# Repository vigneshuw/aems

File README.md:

# AEMS — Autonomous Energy Monitoring System

An open-source, low-cost, modular platform for high-resolution energy monitoring of manufacturing equipment. AEMS acquires three-phase voltage and current through a front end and a 24-bit, simultaneously sampling ADC, managed by a dual-core architecture that separates deterministic acquisition and on-board logging from host communication and control. A host, edge-gateway, and optional cloud software stack enable autonomous, long-duration acquisition independent of a continuously connected host, combining research-grade fidelity with industrial deployability for Industry 4.0 environments.

This repository accompanies the paper (preprint):

> **An Open-Source, Autonomous Platform for High-Resolution Energy Monitoring in Manufacturing**
> Vignesh Selvaraj, Aditya Nagaraj, Shengyuan Zhang, Sina Sadeghian, Sangkee Min

If you use this hardware, firmware, or software in your work, please see
[Citation](#citation) and [`CITATION.cff`](CITATION.cff).

---

## Why AEMS

Long-term, robust monitoring of machine energy consumption is difficult: commercial power
meters capable of capturing transient events are expensive, closed, and impractical to deploy
across an entire facility. AEMS was designed to make high-fidelity energy monitoring
**affordable, customizable, and reproducible**, so that small and medium-sized manufacturers
can instrument their equipment and improve data availability for Industry 4.0 analytics.

Design goals:

- **High-rate, simultaneous multi-channel acquisition** of voltage and current signals.
- **Autonomous operation** — capture and log on the board even when a host or network is unavailable, then stream or transfer data later.
- **Modular and open** — hardware, firmware, and host software are all open and independently reusable.
- **Deployable at scale** — many boards can share a network and be controlled from a single host or from an edge computer such as Raspberry Pi.

---

## System overview

AEMS is organized into three layers, each of which lives in this repository:

| Layer | Location | Role |
|---|---|---|
| **Hardware** | [`hardware/`](hardware/) | Custom AEMS v2 DAQ board — KiCad design, ADS131M08 analog front end, surge protection, impedance-controlled PCB. |
| **Firmware** | [`firmware/`](firmware/) | STM32H745 dual-core firmware. **CM4** owns deterministic acquisition + eMMC storage; **CM7** owns Ethernet/TCP + host command/control over OpenAMP. |
| **Host software** | [`firmware/BoardInterfaceLibrary/`](firmware/BoardInterfaceLibrary/) | Python `board_interface` library, examples, Raspberry Pi daemon (`aemsctl`), and an optional AWS IoT cloud agent. |

```
Machine mains ──▶ AEMS board (ADS131M08 front end)
                        │
                   STM32H745
              ┌─────────┴─────────┐
        CM4 (DAQ + eMMC)   CM7 (Ethernet/TCP)
                        │
                Host (PC / Raspberry Pi)
             board_interface  ·  aemsctl daemon
```

Data flows from the analog front end through the ADS131M08 acquisition path on CM4, is logged
to on-board eMMC and/or streamed over TCP to a host, and can optionally be forwarded to the
cloud for remote monitoring and transfer.

---

## Repository layout

```
aems/
├── hardware/                     KiCad project for the AEMS v2 board
│   ├── *.kicad_sch / *.kicad_pcb Schematics and PCB layout
│   ├── CustomLibs/               Project symbol/footprint libraries
│   ├── LTSpiceSimulation/        Analog front-end simulations (CT op-amp, etc.)
│   ├── DesignSummary/            Stackup, impedance control, interactive BOM (ibom.html)
│   ├── Manufacturing/            PCBWay fabrication outputs
│   └── FutureUpdates/            Planned revisions (e.g. front-end isolation)
│
└── firmware/                     STM32H745 dual-core firmware + host tooling
    ├── CM4/                      Cortex-M4: DAQ, ADS131M08, eMMC/FatFs, OpenAMP
    ├── CM7/                      Cortex-M7: Ethernet/TCP, FreeRTOS, OpenAMP master
    ├── Common/                   Shared cross-core headers/data structures
    ├── BoardInterfaceLibrary/    Python host library, CLI, Raspberry Pi daemon, cloud agent
    ├── docs/Software/            Firmware architecture documentation
    └── UnitTests/                Bench connectivity/test scripts
```

Detailed documentation already lives with each subtree:

- **Firmware architecture** — [`firmware/README.md`](firmware/README.md) and
  [`firmware/docs/Software/README.md`](firmware/docs/Software/README.md)
- **Host Python library** — [`firmware/BoardInterfaceLibrary/README.md`](firmware/BoardInterfaceLibrary/README.md)
- **Raspberry Pi server & cloud** —
  [`firmware/BoardInterfaceLibrary/docs/raspberry_pi_server.md`](firmware/BoardInterfaceLibrary/docs/raspberry_pi_server.md),
  [`firmware/BoardInterfaceLibrary/docs/cloud_autonomy.md`](firmware/BoardInterfaceLibrary/docs/cloud_autonomy.md)
- **Hardware** — [`hardware/README.md`](hardware/README.md)

---

## Hardware at a glance

The AEMS v2 board is built around:

- **ADS131M08** 8-channel, 24-bit simultaneous-sampling delta-sigma ADC as the analog front end.
- **STM32H745** dual-core (Cortex-M7 + Cortex-M4) microcontroller.
- **Isolated power rails** and impedance-controlled routing for Ethernet and USB.
- **MOV-based surge protection** on the measurement inputs.
- **On-board eMMC** storage for logging, plus Ethernet connectivity.

The current firmware and host workflows target a **6-channel acquisition mask (`0x3F`)** — three voltage and three current channels. See [`hardware/README.md`](hardware/README.md) for the board description, bill of materials, and manufacturing notes.

> **Note on voltage range:** the present hardware is validated for direct measurement at the
> board's rated input topology. Higher line-to-line service voltages (e.g. 480 V L-L) require updating the MOV-based surge protector or an external potential transformer, consistent with the modular design; see
> [`hardware/FutureUpdates/`](hardware/FutureUpdates/).

---

## Getting started

The fastest path depends on what you want to do.

**Bring up a board and capture data**

1. Read the system split in [`firmware/docs/Software/README.md`](firmware/docs/Software/README.md).
2. Build and flash the CM4/CM7 firmware from STM32CubeIDE ([`firmware/`](firmware/)).
3. Confirm connectivity with `firmware/UnitTests/tcptest.py` or the Python examples.
4. Use the [`board_interface`](firmware/BoardInterfaceLibrary/) library for repeatable host-side
   control, logging, and streaming.

**Reproduce or modify the hardware**

1. Open the KiCad project in [`hardware/`](hardware/).
2. Review the interactive BOM at `hardware/DesignSummary/ibom.html` and the stackup/impedance
   summaries.
3. Use the [`hardware/Manufacturing/`](hardware/Manufacturing/) outputs for fabrication.

**Deploy a permanent Raspberry Pi server**

See [`firmware/BoardInterfaceLibrary/docs/raspberry_pi_server.md`](firmware/BoardInterfaceLibrary/docs/raspberry_pi_server.md)
for the `aems-boardd` systemd daemon and `aemsctl` control command, and
[`cloud_autonomy.md`](firmware/BoardInterfaceLibrary/docs/cloud_autonomy.md) for optional AWS
IoT integration.

---

## Repository provenance

`hardware/` and `firmware/` are maintained as independent projects and integrated here via
`git subtree`. Each retains its own commit history and can be developed in isolation.

---

## Citation

If you use AEMS in academic work, please cite the paper and (optionally) the archived software
release. Machine-readable metadata is in [`CITATION.cff`](CITATION.cff).

```bibtex
@misc{selvaraj_aems_2026,
  title   = {An Open-Source, Autonomous Platform for High-Resolution Energy
             Monitoring in Manufacturing},
  author  = {Selvaraj, Vignesh and Nagaraj, Aditya and Zhang, Shengyuan and
             Sadeghian, Sina and Min, Sangkee},
  year    = {2026},
  note    = {Preprint. Department of Mechanical Engineering,
             University of Wisconsin-Madison}
  % arXiv id / journal / doi to be added
}
```

The software itself is archived on Zenodo. Please cite the concept DOI (resolves to the
latest release):

**DOI: [10.5281/zenodo.21383443](https://doi.org/10.5281/zenodo.21383443)**

```bibtex
@software{selvaraj_aems_software,
  author    = {Selvaraj, Vignesh and Nagaraj, Aditya and Zhang, Shengyuan and
               Sadeghian, Sina and Min, Sangkee},
  title     = {AEMS: Autonomous Energy Monitoring System},
  year      = {2026},
  publisher = {Zenodo},
  doi       = {10.5281/zenodo.21383443},
  url       = {https://github.com/vigneshuw/aems}
}
```

The version validated in the paper is v1.0.2 (DOI: [10.5281/zenodo.21383444](https://doi.org/10.5281/zenodo.21383444)).

---

## License

AEMS is released as open hardware and open-source software under a per-material split (full
texts in [`LICENSES/`](LICENSES/), following the [REUSE](https://reuse.software) convention):

| Material | License | Applies to |
|---|---|---|
| Hardware design files | [`CERN-OHL-P-2.0`](LICENSES/CERN-OHL-P-2.0.txt) | [`hardware/`](hardware/) — schematics, PCB, libraries, BOM, fabrication outputs |
| Firmware & host software | [`MIT`](LICENSES/MIT.txt) | original code in [`firmware/`](firmware/) and the Python `BoardInterfaceLibrary` |
| Documentation & figures | [`CC-BY-4.0`](LICENSES/CC-BY-4.0.txt) | READMEs, `docs/`, design summaries |

SPDX expression for the repository: `CERN-OHL-P-2.0 AND MIT AND CC-BY-4.0`. Vendor and
third-party components (ST HAL/CMSIS, FreeRTOS, OpenAMP, FatFs, BlueNRG-2, downloaded KiCad
libraries) retain their own licenses. See [`LICENSE`](LICENSE) for the full overview.

---

## Contact

**Vignesh Selvaraj** — `vselvaraj@wisc.edu`, `vignesh-selvaraj@outlook.com`

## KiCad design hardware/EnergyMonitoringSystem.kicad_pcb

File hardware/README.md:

# AEMS Hardware — Energy Monitoring System Board

KiCad design for the AEMS v2 data-acquisition board: a custom, multi-channel energy-monitoring
front end built around the **ADS131M08** ADC and the **STM32H745** dual-core MCU. This is the
hardware layer of the [Autonomous Energy Monitoring System](../README.md) and is designed to be
reproduced, modified, and manufactured by others.

The KiCad project root is `EnergyMonitoringSystem.kicad_pro`.

---

## Board overview

The board acquires multi-channel voltage and current signals at a high, simultaneous sampling
rate, digitizes them through the ADS131M08 analog front end, and hands the data to the STM32H745
for on-board logging and network streaming.

Key design features:

- **ADS131M08** — 8-channel, 24-bit, simultaneous-sampling delta-sigma ADC front end.
- **STM32H745** dual-core (Cortex-M7 + Cortex-M4) host MCU with eMMC and Ethernet.
- **Isolated power rails** feeding the analog front end and digital domains.
- **Impedance-controlled, multilayer PCB** (100 Ω differential / 50 Ω single-ended Ethernet,
  90 Ω USB) — see the impedance and stackup exports in [`DesignSummary/`](DesignSummary/).
- **MOV-based surge protection** on the measurement inputs.
- **Ethernet** and **on-board eMMC** for autonomous, network-independent logging.

The current firmware/host workflows use a **6-channel acquisition mask (`0x3F`)** — three voltage and three current channels.

> **Input voltage topology:** the present design is validated for its rated direct-measurement
> input topology. Measuring higher line-to-line service voltages (e.g. 480 V L-L) exceeds the
> on-board MOV continuous ratings and requires an updated **MOV surge protector (upto a certain voltage level)** or **external potential transformer**. This is
> consistent with the modular design intent and is tracked under
> [`FutureUpdates/`](FutureUpdates/).

---

## Board Power-Up

Temporarily, due to a design issue, the board needs to be powered on as shown in the figure below. This design issue will be fixed in the next hardware version. 

---

## Project structure

```
hardware/
├── EnergyMonitoringSystem.kicad_pro   KiCad project
├── EnergyMonitoringSystem.kicad_sch   Root schematic
├── EnergyMonitoringSystem.kicad_pcb   PCB layout
├── *.kicad_sch                        Hierarchical sheets (see below)
├── CustomLibs/                        Project symbol/footprint libraries
│   ├── EMS.kicad_sym                  Custom symbols
│   ├── EMS.pretty/                    Custom footprints
│   └── Downloaded/                    Third-party part libs (ADS131M08, MOV, op-amps, …)
├── LTSpiceSimulation/                 Analog front-end simulations (CT op-amp, rough studies)
├── Datasheets/                        Component reference material
├── ApplicationNotes/                  ST H7 hardware development notes
├── DesignSummary/                     Stackup, impedance control, interactive BOM
├── Manufacturing/PCBWay/              Fabrication + assembly outputs (Gerbers, drill, BOM, CPL)
└── FutureUpdates/Planned/             Planned revisions (front-end isolation, etc.)
```

### Schematic sheets

The design is hierarchical. The main functional sheets are:

| Sheet | Function |
|---|---|
| `adc` | ADS131M08 analog front end and signal conditioning |
| `uC` / `uCMain` | STM32H745 microcontroller and support |
| `ethernet` | Ethernet PHY (LAN8742) and magnetics |
| `poe` | Ethernet input (No PoE setup currently) |
| `vr` | Voltage regulation / power rails |
| `emmc` | eMMC storage |
| `sd_card` | SD card interface |
| `usb` | USB interface |
| `bm` | Bluetooth (BlueNRG) module |

---

## Bill of materials

- **Interactive BOM:** open [`DesignSummary/ibom.html`](DesignSummary/ibom.html) in a browser
  for a searchable, click-to-highlight BOM with board placement.
- **Fabrication BOM / placement:**
  [`Manufacturing/PCBWay/EnergyMonitoringSystem.kicad_pcb/PCBWay_bom.csv`](Manufacturing/PCBWay/EnergyMonitoringSystem.kicad_pcb/PCBWay_bom.csv)
  and `PCBWay_positions.csv` (component placement / CPL).

---

## Manufacturing

Ready-to-fabricate outputs (generated for PCBWay) are in
[`Manufacturing/PCBWay/`](Manufacturing/PCBWay/) or you generated your own from the KiCAD project:

- Gerbers (`F_Cu`, `B_Cu`, `In1..In6_Cu`, mask, paste, silkscreen, edge cuts)
- Drill files (`PTH`, `NPTH`)
- `PCBWay_bom.csv` (BOM) and `PCBWay_positions.csv` (pick-and-place)
- `PCBWay_netlist.ipc` (IPC-356 netlist)
- `DesignRequirements.pdf` and `Jump-SolderBridges.png` (assembly notes)

Stackup and impedance targets are documented in [`DesignSummary/`](DesignSummary/)
(`CurrentStackup.png`, `PCBWay Stackup.png`, and the `ImpedanceControl *.png` exports).

To regenerate outputs, open `EnergyMonitoringSystem.kicad_pcb` in KiCad and re-plot Gerbers/drill
and re-export the BOM/placement.

---

## Requirements

- **KiCad 7** or newer to open the project.
- Custom and downloaded libraries under [`CustomLibs/`](CustomLibs/) are referenced via the
  project-local `sym-lib-table` / `fp-lib-table`, so the project should open self-contained.

---

## Future updates

Planned hardware revisions are tracked in [`FutureUpdates/Planned/`](FutureUpdates/Planned/),
including improved analog front-end **isolation** and higher line-to-line voltages.

---

## License

Hardware licensing is being finalized as part of the open-hardware release; see the
[top-level LICENSE](../LICENSE). Please contact the authors before redistributing the design
files until the final license is committed.

For system context, firmware, and host software, see the [top-level README](../README.md).

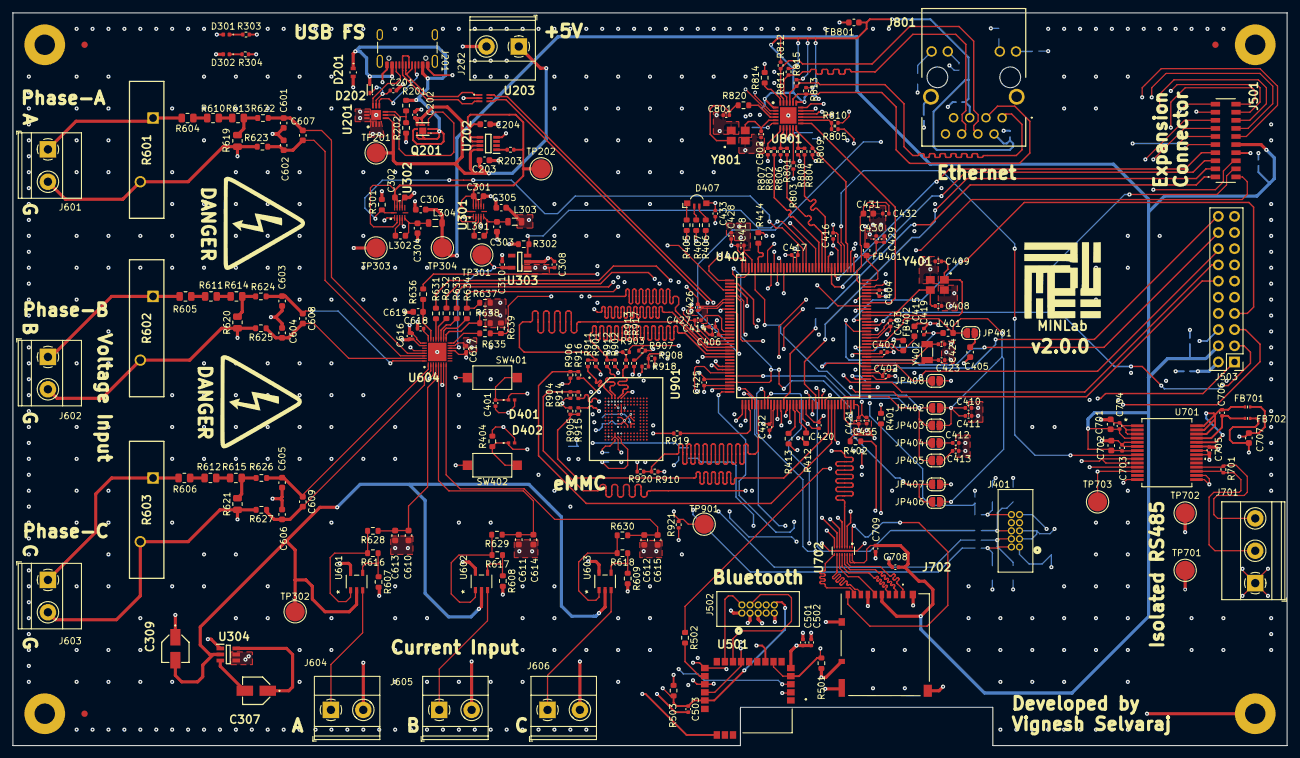
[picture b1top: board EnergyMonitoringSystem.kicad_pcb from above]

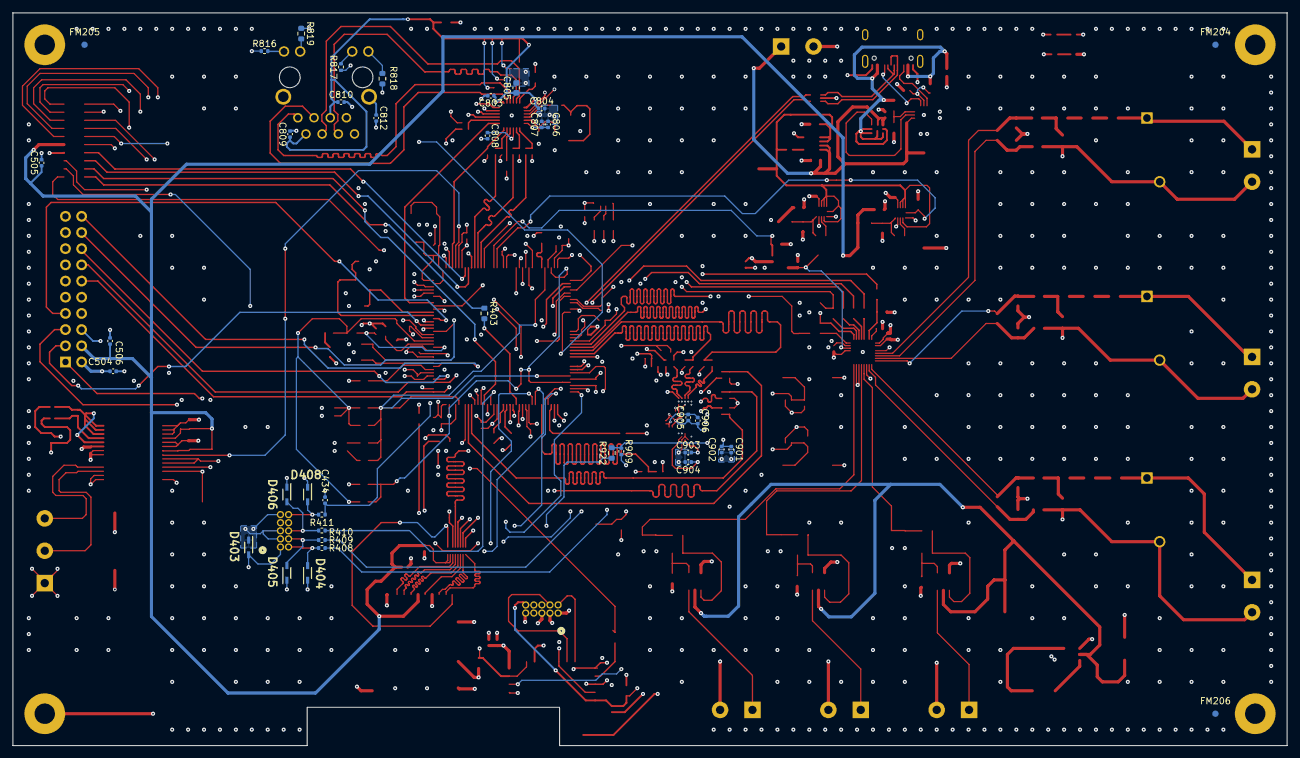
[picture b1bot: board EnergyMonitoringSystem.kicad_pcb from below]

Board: 8 copper layers, 200.0 x 115.0 mm, 294 parts (38 on the bottom side), 213 nets.

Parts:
C201, C202, C401, C402, C403, C404, C407, C414, C416, C417, C418, C420, C421, C422, C425, C426, C427, C430, C432, C433, C434, C502, C503, C504, C505, C506, C708, C709, C803, C804, C808, C809, C810, C901, C903, C905: 100n; C_0402_1005Metric
C203, C204, C301, C302, C405, C415, C431, C701, C702, C707, C805: 10u; C_0603_1608Metric
C303, C304, C305, C306: 47u; C_0603_1608Metric
C307, C309: 10u; 10SVPS10M
C308, C310, C406, C429, C616, C617, C807: 1u; C_0402_1005Metric
C408, C409, C423, C424, C801, C802: 5p6; C_0402_1005Metric
C410, C411: 4u7; C_0402_1005Metric
C412, C413, C428, C435, C501, C902, C904, C906: 2u2; C_0402_1005Metric
C419: 220p; C_0402_1005Metric
C601, C602, C603, C604, C605, C606, C610, C611, C612, C619: 10p; C_0603_1608Metric
C607, C608, C609, C613, C614, C615: 6800p; C_0603_1608Metric
C618: 220n; C_0402_1005Metric
C703, C704, C705, C706: 0u1; C_0402_1005Metric
C806: 470p; C_0402_1005Metric
C812: 1n; C_0402_1005Metric
D201: ESDA7P60-1U1M
D202: BAT30KFILM
D301, D302: LED; LED_0402_1005Metric
D401, D402: ESDALC6V1-1M2; ESDALC6V11M2
D403, D404, D405, D406, D408: PESD3V3L1BA,115; PESD3V3L1BA_115-SOD-323-2
D407: LED_RAGB; LED_Kingbright_APFA3010_3x1.5mm_Horizontal
FB401, FB402, FB801: FerriteBead; L_0603_1608Metric
FB701, FB702: FerriteBead; BLM15HD182SN1D
FM201, FM202, FM203, FM204, FM205, FM206: Fiducial; Fiducial_1mm_Mask2mm
H201, H202, H203, H204: MountingHole_Pad; MountingHole_3.2mm_M3_Pad
J201: USB_C_Receptacle_USB2.0_16P; USB_C_Receptacle_GCT_USB4105-xx-A_16P_TopMnt_Horizontal
J202, J601, J602, J603, J604, J605, J606: Screw_Terminal_01x02; TerminalBlock_Phoenix_MKDS-1,5-2-5.08_1x02_P5.08mm_Horizont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
J401, J502: Conn_02x05_Counter_Clockwise; 62701021621
J501: CLP-110-02-G-D; CLP-110-02-XXX-D
J503: Conn_02x08_Counter_Clockwise; PinHeader_2x10_P2.54mm_Vertical
J701: Screw_Terminal_01x03; TerminalBlock_Phoenix_MKDS-1,5-3-5.08_1x03_P5.08mm_Horizont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
J702: DM3AT-SF-PEJM5_40_; DM3ATSFPEJM540
J801: SI-60062-F; Connector-SI60062F
JP401, JP402, JP403, JP406, JP408: SolderJumper_2_Bridged; SolderJumper-2_P1.3mm_Open_RoundedPad1.0x1.5mm
JP404, JP405, JP407: SolderJumper_2_Open; SolderJumper-2_P1.3mm_Open_RoundedPad1.0x1.5mm
L301, L302, L401: 2u2; L_0603_1608Metric
L303, L304: 10u; L_0805_2012Metric
Q201: STL6N3LLH6
R201, R404, R607, R608, R609, R637: 10k; R_0603_1608Metric
R202: 2k7; R_0603_1608Metric
R203, R701: 120R; R_0402_1005Metric
R301, R302, R638, R639: 100k; R_0603_1608Metric
R303, R304: 220R; R_0402_1005Metric
R401, R402, R403, R502: 22R; R_0603_1608Metric
R405, R406, R407, R622, R623, R624, R625, R626, R627: 1k; R_0603_1608Metric
R408, R409, R410, R411, R811, R812, R813, R815: 49R9; R_0402_1005Metric
R412, R413, R414, R631, R632, R633, R634, R635, R636: 33R; R_0603_1608Metric
R501: 47k; R_0603_1608Metric
R503: 4k7; R_0603_1608Metric
R601, R602, R603: R_Variable; B72220S0271K101
R604, R605, R606, R610, R611, R612, R613, R614, R615: 330k; R_0805_2012Metric
R616, R617, R618: 15k; R_0603_1608Metric
R619, R620, R621: 750R; R_0805_2012Metric
R628, R629, R630: 2k; R_0603_1608Metric
R801, R802, R804, R805: 33R; R_0402_1005Metric
R803, R806, R807, R808, R810, R816, R817, R910: 10k; R_0402_1005Metric
R809: 1k5; R_0402_1005Metric
R814: 12k1; R_0603_1608Metric
R818, R819: 270R; R_0603_1608Metric
R820, R922: 0R; R_0603_1608Metric
R901, R902, R903, R904, R905, R906, R907, R908, R909, R921: 47k; R_0402_1005Metric
R911, R912, R913, R914, R915, R916, R917, R918, R919, R920: 22R; R_0402_1005Metric
SW401, SW402: SW_Push; SW_SPST_CK_RS282G05A3
TP201, TP202, TP301, TP302, TP303, TP304, TP701, TP702, TP703, TP901: TestPoint; TestPoint_Pad_D3.0mm
U201: TCPP01-M12; TCPP01-M12-QFN-12L
U202: STEF05SGR; STEF05SGR-TSOT23-8L
U203: USBLC6-2P6; USBLC62P6-SOT666-6
U301, U302: ST1PS02CQTR
U303: LDLN025M12R; LDLN025M12R-SOT-23-5
U304: LM2664M6_NOPB; LM2664M6_NOPB-SOT-23-6
U401: STM32H745ZGT6; STM32H745ZGT6_LQFP144
U501: BLUENRG-M2SA
U601, U602, U603: TSV911ILT; TSV911ILT_SOT23-5
U604: ADS131M08IRSNR; ADS131M08IRSNR-QFN40
U701: ADM2565EBRNZ; ADM2565EBRNZ-SOIC-28
U702: EMIF06-MSD02N16
U801: LAN8742A-CZ-TR; LAN8742A-CZ-TR_QFN50
U901: MX52LM04A11XSI; MX52LM04A11XSI_BGA153
Y401, Y801: Crystal_GND24; NX3225SA25000MSTDCSR6
Y402: 32.768KHz; Crystal_SMD_3215-2Pin_3.2x1.5mm

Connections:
+1V2: C310.1, TP301.1, U303.5 (OUT), U604.14 (REFIN)
+5V: C204.1, C301.1, C302.1, R203.1, TP202.1, U202.5 (SOURCE_1), U202.6 (SOURCE_2), U301.2 (VIN), U301.9 (D0), U301.10 (D1), U301.11 (D2), U301.12 (EN), U302.2 (VIN), U302.9 (D0), U302.10 (D1), U302.11 (D2)
+5V_EXT: C202.1, C203.1, J202.1, Q201.4 (S_1), Q201.8 (S_2), TP201.1, U201.4 (SOURCE), U202.7 (VCC_1), U202.8 (VCC_2)
+DCDC_1: C305.1, C308.1, C402.1, C403.1, C404.1, C406.1, C407.1, C414.1, C416.1, C417.1, C418.1, C420.1, C421.1, C422.1, C425.1, C426.1, C427.1, C428.2, C433.1, C435.2, C501.1, C502.1, C504.1, C616.2, C617.2, C808.1, C903.1, C904.1, C905.1, C906.1, D301.2 (A), D403.2 (K2), D407.2 (A), FB401.1, FB402.1, FB801.1, J401.1, J502.1, J503.2, JP407.1 (A), JP408.1 (A), L303.2, R503.2, R637.2, R638.2, R639.2, R806.2, R807.2, R808.2, R809.2, R810.2, R901.2, R902.2, R903.2, R904.2, R905.2, R906.2, R907.2, R908.2, R909.2, R910.2, SW402.2, TP303.1, U303.1 (IN), U304.4 (SD), U304.5 (V+), U401.7 (VDD_1), U401.13 (VDD_2), U401.19 (VDD_3), U401.32 (VDD_4), U401.42 (VDD_5), U401.56 (VDD_6), U401.71 (VDD_7), U401.79 (VDD_8), U401.90 (VDD50USB), U401.91 (VDD33USB), U401.92 (VDD_9), U401.106 (VDD_10), U401.119 (VDD_11), U401.129 (VDD_12), U401.144 (VDD_13), U501.5 (VIN), U601.5 (VCC+), U602.5 (VCC+), U603.5 (VCC+), U604.15 (AVDD), U604.26 (DVDD), U801.9 (VDDIO), U901.C6 (VCCQ_1), U901.E6 (VCC_1), U901.F5 (VCC_2), U901.J10 (VCC_3), U901.K9 (VCC_4), U901.M4 (VCCQ_2), U901.N4 (VCCQ_3), U901.P3 (VCCQ_4), U901.P5 (VCCQ_5)
+DCDC_2: C306.1, C505.1, C506.1, C701.1, C702.2, C703.1, C704.2, C708.1, C709.1, D302.2 (A), J501.10, J503.4, J702.4 (VDD), L304.2, TP304.1, U701.4 (VCC), U701.7 (VIO), U702.15 (VCC), U702.16 (RDATA_VCC)
+VBUSc: D201.1 (K), D202.2 (A), J201.A4 (VBUS), J201.A9 (VBUS), J201.B4 (VBUS), J201.B9 (VBUS), Q201.1 (D_1), Q201.2 (D_2), Q201.5 (D_3), Q201.6 (D_4), Q201.7 (D_5), R201.1
+VDD_SDC: C410.2, C411.2, JP401.2 (B), JP402.1 (A), JP403.1 (A), JP406.1 (A), L401.1, U401.17 (VFBSMPS)
+VREF: C429.1, C430.1, C431.1, C432.1, FB401.2, U401.35 (VREF+), U401.36 (VDDA)
+V_ISO: C705.1, C707.2, FB702.2, TP701.1, U701.23 (VISOIN)
-DCDC_1: C309.2, TP302.1, U304.2 (OUT), U601.2 (VCC-), U602.2 (VCC-), U603.2 (VCC-)
/ADC/CLKIN_ADS_T: C619.1, R636.2, U604.23 (XTAL1_CLKIN)
/ADC/CT_PhaseA_Amp_OUT: R616.2, R628.2, U601.1 (OUT)
/ADC/CT_PhaseA_IN: J604.1, U601.3 (IN+)
/ADC/CT_PhaseB_Amp_OUT: R617.2, R629.2, U602.1 (OUT)
/ADC/CT_PhaseB_IN: J605.1, U602.3 (IN+)
/ADC/CT_PhaseC_Amp_OUT: R618.2, R630.2, U603.1 (OUT)
/ADC/CT_PhaseC_IN: J606.1, U603.3 (IN+)
/ADC/DIN_ADS_T: R631.2, U604.21 (DIN)
/ADC/DOUT_ADS_T: R632.2, U604.20 (DOUT)
/ADC/DRDY_ADS_T: R634.2, U604.18 (DRDY_N)
/ADC/I_Phase_A_P: C610.1, C613.1, R628.1, U604.4 (AIN3P)
/ADC/I_Phase_B_P: C611.1, C614.1, R629.1, U604.5 (AIN4P)
/ADC/I_Phase_C_P: C612.1, C615.1, R630.1, U604.8 (AIN5P)
/ADC/SCK_ADS_T: R633.2, U604.19 (SCLK)
/ADC/SYNC_RESET_ADS_T: R635.2, U604.16 (SYNC_RESET_N)
/ADC/V_Phase_A_N: C602.2, C607.2, R623.1, U604.30 (AIN0N)
/ADC/V_Phase_A_P: C601.1, C607.1, R622.1, U604.29 (AIN0P)
/ADC/V_Phase_B_N: C604.2, C608.2, R625.1, U604.31 (AIN1N)
/ADC/V_Phase_B_P: C603.1, C608.1, R624.1, U604.32 (AIN1P)
/ADC/V_Phase_C_N: C606.2, C609.2, R627.1, U604.2 (AIN2N)
/ADC/V_Phase_C_P: C605.1, C609.1, R626.1, U604.1 (AIN2P)
/BLE/BLE_SWDCLK: J502.4, U501.12 (DIO9)
/BLE/BLE_SWDIO: J502.2, U501.13 (DIO10)
/BLE/SPI5_MISO_R: R502.2, U501.16 (DIO2)
/ETHERNET/ETH_DCDC2_FR: C803.1, C804.1, C805.1, C809.1, C810.1, FB801.2, J801.2 (TCT), J801.5 (RCT), R811.2, R812.2, R813.2, R815.2, U801.1 (VDD2A), U801.19 (VDD1A)
/ETHERNET/RMII_CRS_DV_R: R804.2, R808.1, U801.11 (CRS_DV/MODE2)
/ETHERNET/RMII_PHYAD0: R803.2, U801.10 (RXER/PHYAD0)
/ETHERNET/RMII_REF_CLK_R: R805.2, R810.1, U801.14 (NINT/REFCLKO)
/ETHERNET/RMII_RXD0_R: R801.2, R806.1, U801.8 (RXD0/MODE0)
/ETHERNET/RMII_RXD1_R: R802.2, R807.1, U801.7 (RXD1/MODE1)
/ETHERNET/RMII_RXN: J801.6 (RD-), R811.1, U801.22 (RXN)
/ETHERNET/RMII_RXP: J801.4 (RD+), R812.1, U801.23 (RXP)
/ETHERNET/RMII_TXN: J801.3 (TD-), R813.1, U801.20 (TXN)
/ETHERNET/RMII_TXP: J801.1 (TD+), R815.1, U801.21 (TXP)
/ETHERNET/RMII_XTAL1: C802.2, U801.5 (XTAL1/CLKIN), Y801.3
/ETHERNET/RMII_XTAL2: R820.2, U801.4 (XTAL2)
/SDCARD/SD_CLK: J702.5 (CLK), U702.11 (CLK_EX)
/SDCARD/SD_CMD: J702.3 (CMD), U702.12 (CMD_EX)
/SDCARD/SD_DAT0: J702.7 (DAT0), U702.10 (DAT0_EX)
/SDCARD/SD_DAT1: J702.8 (DAT1), U702.9 (DAT1_EX)
/SDCARD/SD_DAT2: J702.1 (DAT2), U702.14 (DAT2_EX)
/SDCARD/SD_DAT3: J702.2 (CD/DAT3), U702.13 (DAT3_EX)
/USB/FSE_I_LIM: R203.2, U202.1 (I_LIM)
/USB/PD_GATE: Q201.3 (G), U201.5 (GATE)
/USB/PD_IN_GD: C201.1, D202.1 (K), U201.8 (IN_GD)
/USB/PD_VBUS_CTRL: R201.2, R202.1, U201.6 (VBUS_CTRL)
/USB/USB_CC1c: J201.A5 (CC1), U201.7 (CC1C)
/USB/USB_CC2c: J201.B5 (CC2), U201.9 (CC2C)
/USB/USB_OTG_D+: J201.A6 (D+), J201.B6 (D+), U203.3 (I/O2_1)
/USB/USB_OTG_D-: J201.A7 (D-), J201.B7 (D-), U203.1 (I/O1_1)
/VR/CHRG_CAP+: C307.1, U304.6 (CAP+)
/VR/CHRG_CAP-: C307.2, U304.3 (CAP-)
/VR/DC1_SW: L301.1, U301.3 (SW)
/VR/DC1_VOUT: C303.1, L301.2, L303.1, U301.5 (VOUT)
/VR/DC2_SW: L302.1, U302.3 (SW)
/VR/DC2_VOUT: C304.1, L302.2, L304.1, U302.5 (VOUT)
/eMMC/SDMMC1_CK_R: R919.2, U901.M6 (CLK)
/eMMC/SDMMC1_CMD_R: R920.2, U901.M5 (CMD)
/eMMC/SDMMC1_D0_R: R911.2, U901.A3 (DAT0)
/eMMC/SDMMC1_D1_R: R912.2, U901.A4 (DAT1)
/eMMC/SDMMC1_D2_R: R913.2, U901.A5 (DAT2)
/eMMC/SDMMC1_D3_R: R914.2, U901.B2 (DAT3)
/eMMC/SDMMC1_D4_R: R915.2, U901.B3 (DAT4)
/eMMC/SDMMC1_D5_R: R916.2, U901.B4 (DAT5)
/eMMC/SDMMC1_D6_R: R917.2, U901.B5 (DAT6)
/eMMC/SDMMC1_D7_R: R918.2, U901.B6 (DAT7)
/eMMC/SDMMC1_eMMC_RSTn_JP: R909.1, R922.2, U901.K5 (RST_N)
/eMMC/VDDI: C901.1, C902.1, U901.C2 (VDDI)
/uCMain/BOOT0: D402.1 (K), R404.2, SW402.1, U401.135 (BOOT0)
/uCMain/DEBUG_JTCK-SWCLK: R409.1, U401.107 (PA14)
/uCMain/DEBUG_JTCK-SWCLK-H: D405.2 (K2), J401.4, R409.2
/uCMain/DEBUG_JTDO-SWO: R410.1, U401.130 (PB3)
/uCMain/DEBUG_JTDO-SWO-H: D406.2 (K2), J401.6, R410.2
/uCMain/DEBUG_JTMS-SWDIO: R408.1, U401.102 (PA13)
/uCMain/DEBUG_JTMS-SWDIO-H: D404.2 (K2), J401.2, R408.2
/uCMain/NRST: C401.1, C434.1, D401.1 (K), R411.1, SW401.1, U401.27 (NRST)
/uCMain/NRST-H: D408.2 (K2), J401.10, R411.2
/uCMain/OSC32_IN: C423.1, U401.10 (PC14-OSC32_IN), Y402.1
/uCMain/OSC32_OUT: C424.1, U401.11 (PC15-OSC32_OUT), Y402.2
/uCMain/OSC_IN: C409.2, U401.25 (PH0-OSC_IN), Y401.1
/uCMain/OSC_OUT: C408.2, U401.26 (PH1-OSC_OUT), Y401.3
/uCMain/SPI5_MOSI_R: R402.1, U401.23 (PF9)
/uCMain/SPI5_SCK_R: R401.1, U401.21 (PF7)
/uCMain/TIM1_CH1: R405.2, U401.59 (PE9)
/uCMain/TIM1_CH2: R406.2, U401.61 (PE11)
/uCMain/TIM1_CH3: R407.2, U401.63 (PE13)
ADC1_INP9: J501.11, U401.49 (PB0)
ADC3_INP1: J501.9, U401.31 (PC3_C)
ADS_CS: J503.18, R638.1, U401.20 (PF6), U604.17 (CS_N)
ADS_DIN_uC_DOUT: J503.16, R631.1, U401.5 (PE6)
ADS_DOUT_uC_DIN: J503.14, R632.1, U401.4 (PE5)
ADS_DRDY: J503.20, R634.1, R637.1, U401.9 (PC13)
ADS_SPI_SCK: J503.12, R633.1, U401.1 (PE2)
ADS_STM32_CLKOUT: R636.1, U401.97 (PA8)
ADS_SYNC_RESET: R635.1, R639.1, U401.28 (PC0)
BLE_INT: R501.2, U401.2 (PE3), U501.4 (DIO5), U501.7 (DIO7/BOOT)
BLE_RST: C503.1, J502.10, R503.1, U401.76 (PD8), U501.19 (RESETN)
BLE_TEST8: U401.78 (PD10), U501.2 (ADC1)
BLE_TEST9: U401.77 (PD9), U501.3 (DIO4)
DCDC_2_EN: R301.1, U302.12 (EN), U401.53 (PF14)
ETH_NRST: U401.45 (PA6), U801.15 (NRST)
FDCAN2_RX: J501.16, U401.72 (PB12)
FDCAN2_TX: J501.18, U401.73 (PB13)
GND: C201.2, C202.2, C203.2, C204.2, C301.2, C302.2, C303.2, C304.2, C305.2, C306.2, C308.2, C309.1, C310.2, C401.2, C402.2, C403.2, C404.2, C405.1, C406.2, C407.2, C408.1, C409.1, C410.1, C411.1, C412.1, C413.1, C414.2, C415.1, C416.2, C417.2, C418.2, C419.1, C420.2, C421.2, C422.2, C423.2, C424.2, C425.2, C426.2, C427.2, C428.1, C429.2, C430.2, C431.2, C432.2, C433.2, C434.2, C435.1, C501.2, C502.2, C503.2, C504.2, C505.2, C506.2, C601.2, C602.1, C603.2, C604.1, C605.2, C606.1, C610.2, C611.2, C612.2, C613.2, C614.2, C615.2, C616.1, C617.1, C618.2, C619.2, C701.2, C702.1, C703.2, C704.1, C708.2, C709.2, C801.1, C802.1, C803.2, C804.2, C805.2, C806.2, C807.2, C808.2, C809.2, C810.2, C812.2, C901.2, C902.2, C903.2, C904.2, C905.2, C906.2, D201.2 (A), D401.2 (A), D402.2 (A), D403.1 (K1), D404.1 (K1), D405.1 (K1), D406.1 (K1), D408.1 (K1), H201.1, H202.1, H203.1, H204.1, J201.A1 (GND), J201.A12 (GND), J201.B1 (GND), J201.B12 (GND), J201.S1 (SHIELD), J202.2, J401.3, J401.5, J401.9, J501.8, J502.3, J502.5, J502.9, J503.6, J601.2, J602.2, J603.2, J604.2, J605.2, J606.2, J702.6 (VSS), J702.MP1, J702.MP2, J702.MP3, J702.MP4, J702.MP5, J801.8, R202.2, R301.2, R302.1, R303.2, R304.2, R404.1, R501.1, R601.2, R602.2, R603.2, R607.2, R608.2, R609.2, R619.1, R620.1, R621.1, R623.2, R625.2, R627.2, R803.1, R814.2, R816.1, R817.1, R818.1, R819.1, R921.1, SW401.2, U201.1 (CC2), U201.2 (GND), U201.3 (CC1), U201.10 (DB/), U201.11 (FLT/), U201.12 (VCC), U201.13 (EP), U202.4 (GND), U203.2 (GND), U301.1 (AUX), U301.4 (GND), U301.8 (CL), U302.1 (AUX), U302.4 (GND), U302.8 (CL), U303.2 (GND), U304.1 (GND), U401.6 (VSS_1), U401.12 (VSS_2), U401.14 (VSSSMPS), U401.18 (VSS_3), U401.33 (VSS_4), U401.34 (VSSA), U401.41 (VSS_5), U401.55 (VSS_6), U401.69 (VSS_7), U401.80 (VSS_8), U401.89 (VSS_9), U401.104 (VSS_10), U401.118 (VSS_11), U401.128 (VSS_12), U401.141 (VSS_13), U501.8 (GND_1), U501.21 (GND_2), U604.3 (AIN3N), U604.6 (AIN4N), U604.7 (AIN5N), U604.13 (AGND), U604.25 (DGND), U604.28 (AGND), U604.33 (EP), U701.1 (GND1), U701.2 (GND1), U701.3 (GND1), U701.5 (GND1), U701.6 (GND1), U701.14 (GND1), U702.17 (EP_(GND)), U801.25 (EP), U901.A6 (VSS_1), U901.C4 (VSSQ_1), U901.E7 (VSS_2), U901.G5 (VSS_3), U901.H10 (VSS_4), U901.J5 (VSS_5), U901.K8 (VSS_6), U901.N2 (VSSQ_2), U901.N5 (VSSQ_3), U901.P4 (VSSQ_4), U901.P6 (VSSQ_5), Y401.2, Y401.4, Y801.2, Y801.4
GND2: C705.2, C707.1, FB701.2, J701.1, TP702.1, U701.15 (GND2), U701.16 (GND2), U701.21 (GND2), U701.22 (GND2)
GPIO_IN_1: J501.19, U401.62 (PE12)
GPIO_IN_2: J501.17, U401.64 (PE14)
GPIO_OUT_1: J501.20, U401.60 (PE10)
I2C1_SCL: J501.15, U401.133 (PB6)
I2C1_SDA: J501.13, U401.134 (PB7)
LDO_EN: R302.2, U303.3 (EN), U401.52 (PF11)
unnamed: C801.2, R820.1, Y801.1
unnamed: C812.1, J801.9, J801.10
unnamed: D301.1 (K), R303.1
unnamed: D302.1 (K), R304.1
unnamed: D407.4 (BK), R407.1
unnamed: D407.3 (GK), R406.1
unnamed: D407.1 (RK), R405.1
unnamed: J601.1, R601.1, R604.2
unnamed: J602.1, R602.1, R605.2
unnamed: J603.1, R603.1, R606.2
unnamed: J701.2, R701.1, U701.17 (A)
unnamed: J701.3, R701.2, U701.18 (B)
unnamed: J801.13 (GRN_+), R817.2, U801.2 (LED2/NINT/NPME/NINTSEL)
unnamed: J801.14 (GRN_-), R818.2
unnamed: J801.11 (YEL_+), R816.2, U801.3 (LED1/NINT/NPME/REGOFF)
unnamed: J801.12 (YEL_-), R819.2
unnamed: C405.2, JP401.1 (A)
unnamed: JP402.2 (B), JP403.2 (B), JP404.2 (B), JP405.2 (B), U401.68 (VCAP_1), U401.103 (VCAP_2), U401.140 (VCAP_3)
unnamed: C412.2, JP404.1 (A)
unnamed: C413.2, JP405.1 (A)
unnamed: JP406.2 (B), JP407.2 (B), U401.70 (VDDLDO_1), U401.105 (VDDLDO_2), U401.143 (VDDLDO_3)
unnamed: JP408.2 (B), U401.8 (VBAT)
unnamed: R604.1, R610.2
unnamed: R605.1, R611.2
unnamed: R606.1, R612.2
unnamed: R610.1, R613.2
unnamed: R611.1, R614.2
unnamed: R612.1, R615.2
unnamed: R613.1, R619.2, R622.2
unnamed: R614.1, R620.2, R624.2
unnamed: R615.1, R621.2, R626.2
unnamed: R414.2, U401.67 (PB11)
unnamed: R403.2, U401.122 (PG9)
unnamed: R413.1, U401.125 (PG12)
unnamed: R412.1, U401.126 (PG13)
unnamed: C415.2, FB402.2, U401.16 (VDDSMPS)
unnamed: C419.2, L401.2, U401.15 (VLXSMPS)
unnamed: R607.1, R616.1, U601.4 (IN-)
unnamed: R608.1, R617.1, U602.4 (IN-)
unnamed: R609.1, R618.1, U603.4 (IN-)
unnamed: C618.1, U604.24 (CAP)
unnamed: C706.2, FB702.1, U701.25 (VISOOUT)
unnamed: C706.1, FB701.1, U701.24 (GNDISO), U701.26 (GNDISO), U701.27 (VSEL), U701.28 (GNDISO)
unnamed: R814.1, U801.24 (RBIAS)
unnamed: C806.1, C807.1, U801.6 (VDDCR)
unnamed: R921.2, TP901.1, U901.H5 (DATA_STROBE)
RMII_CRS_DV: R804.1, U401.46 (PA7)
RMII_MDC: U401.29 (PC1), U801.13 (MDC)
RMII_MDIO: R809.1, U401.39 (PA2), U801.12 (MDIO)
RMII_REF_CLK: R805.1, U401.38 (PA1)
RMII_RXD0: R801.1, U401.47 (PC4)
RMII_RXD1: R802.1, U401.48 (PC5)
RMII_TXD0: R412.2, U801.17 (TXD0)
RMII_TXD1: R413.2, U801.18 (TXD1)
RMII_TX_EN: R414.1, U801.16 (TXEN)
SDMMC1_CK: R919.1, U401.111 (PC12)
SDMMC1_CMD: R910.1, R920.1, U401.114 (PD2)
SDMMC1_D0: R901.1, R911.1, U401.95 (PC8)
SDMMC1_D1: R902.1, R912.1, U401.96 (PC9)
SDMMC1_D2: R903.1, R913.1, U401.109 (PC10)
SDMMC1_D3: R904.1, R914.1, U401.110 (PC11)
SDMMC1_D4: R905.1, R915.1, U401.136 (PB8)
SDMMC1_D5: R906.1, R916.1, U401.137 (PB9)
SDMMC1_D6: R907.1, R917.1, U401.93 (PC6)
SDMMC1_D7: R908.1, R918.1, U401.94 (PC7)
SDMMC2_CK: U401.120 (PD6), U702.6 (CLK_IN)
SDMMC2_CMD: U401.121 (PD7), U702.5 (CMD_IN)
SDMMC2_D0: U401.74 (PB14), U702.7 (DAT0_IN)
SDMMC2_D1: U401.75 (PB15), U702.8 (DAT1_IN)
SDMMC2_D2: U401.124 (PG11), U702.3 (DAT2_IN)
SDMMC2_D3: U401.131 (PB4), U702.4 (DAT3_IN)
SD_DETECT: J702.CD1 (CARD_DETECT), U401.123 (PG10), U702.1 (WP/CD)
SPI1_MISO: J501.1, R403.1
SPI1_MOSI: J501.3, U401.132 (PB5)
SPI1_NSS: J501.7, U401.43 (PA4)
SPI1_SCK: J501.5, U401.44 (PA5)
SPI5_CS: J503.7, U401.24 (PF10), U501.11 (DIO11), U501.18 (DIO1)
SPI5_MISO: J503.3, R502.1, U401.22 (PF8)
SPI5_MOSI: J503.5, R402.2, U501.17 (DIO3)
SPI5_SCK: J503.1, R401.2, U501.15 (DIO0)
TIM4_CH1: J501.14, U401.82 (PD12)
TIM4_CH2: J501.12, U401.83 (PD13)
UART4_DE: J501.4, U401.108 (PA15)
UART4_RX: J501.6, U401.112 (PD0)
UART4_TX: J501.2, U401.37 (PA0)
USART2_DE: U401.116 (PD4), U701.9 (*RE), U701.10 (DE)
USART2_INV_485: TP703.1, U401.113 (PD1), U701.12 (INV)
USART2_RX: U401.40 (PA3), U701.8 (RXD)
USART2_TX: U401.117 (PD5), U701.11 (TXD)
eMMC_RSTn: R922.1, U401.138 (PE0)
uC_OTG_D+: U203.4 (I/O2_2), U401.101 (PA12)
uC_OTG_D-: U203.6 (I/O1_2), U401.100 (PA11)

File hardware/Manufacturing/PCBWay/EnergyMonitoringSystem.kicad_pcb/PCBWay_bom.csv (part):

Designator,Quantity,Value,Footprint,Package,MPN,DNP,Mount_Type,Description,Distributor_Link,Manufacturer_Name,Mouser Part Number,Mouser Price/Stock,Height
"C201, C202, C401, C402, C403, C404, C407, C414, C416, C417, C418, C420, C421, C422, C425, C426, C427, C430, C432, C433, C434, C502, C503, C504, C505, C506, C708, C709, C803, C804, C808, C809, C810, C901, C903, C905",36,100n,C_0402_1005Metric,,04023C104KAT2A,,smt,Unpolarized capacitor,https://www.mouser.com/ProductDetail/KYOCERA-AVX/04023C104KA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,KYOCERA AVX,,,
"C203, C204, C301, C302, C405, C415, C431, C701, C702, C707, C805",11,10u,C_0603_1608Metric,,KGM15CR51A106KT,,smt,Unpolarized capacitor,https://www.mouser.com/ProductDetail/KYOCERA-AVX/KGM15CR51A1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,KYOCERA AVX,,,
"C303, C304, C305, C306",4,47u,C_0603_1608Metric,,KGM15CR50J476MT,,smt,Unpolarized capacitor,https://www.mouser.com/ProductDetail/KYOCERA-AVX/KGM15CR50J4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,KYOCERA AVX ,,,
"C307, C309",2,10u,10SVPS10M,,10SVPS10M,,smt,"Polarized capacitor, US symbol",https://www.mouser.com/ProductDetail/Panasonic/10SVPS10M?qs=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,Panasonic,,,
"C308, C310, C406, C429, C616, C617, C807",7,1u,C_0402_1005Metric,,KGM05AR70J105KH,,smt,Unpolarized capacitor,https://www.mouser.com/ProductDetail/KYOCERA-AVX/KGM05AR70J1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,KYOCERA AVX ,,,
"C408, C409, C423, C424, C801, C802",6,5p6,C_0402_1005Metric,,GJM1555C1H5R6FB01D,,smt,Unpolarized capacitor,https://www.mouser.com/ProductDetail/Murata-Electronics/GJM1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,Murata Electronics,,,
"C410, C411",2,4u7,C_0402_1005Metric,,KAM05CT70J475KH,,smt,Unpolarized capacitor,https://www.mouser.com/ProductDetail/KYOCERA-AVX/KAM05CT70J4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,KYOCERA AVX,,,
"C412, C413, C428, C435, C501, C902, C904, C906",8,2u2,C_0402_1005Metric,,KGM05AR51A225KH,,smt,Unpolarized capacitor,https://www.mouser.com/ProductDetail/KYOCERA-AVX/KGM05AR51A2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,KYOCERA AVX,,,
C419,1,220p,C_0402_1005Metric,,CC0402JRNPO9BN221,,smt,Unpolarized capacitor,https://www.mouser.com/ProductDetail/YAGEO/CC0402JRNPO9BN221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,YAGEO,,,
"C601, C602, C603, C604, C605, C606, C610, C611, C612, C619",10,10p,C_0603_1608Metric,,GCM1885C2A100JA16D,,smt,Unpolarized capacitor,https://www.mouser.com/ProductDetail/Murata-Electronics/GCM1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,Murata Electronics,,,
"C607, C608, C609, C613, C614, C615",6,6800p,C_0603_1608Metric,,CGA3EANP02A682J080AC,,smt,Unpolarized capacitor,https://www.mouser.com/ProductDetail/TDK/CGA3EANP02A682J080A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,TDK,,,
C618,1,220n,C_0402_1005Metric,,CGA2B2X7R1C224K050BE,,smt,Unpolarized capacitor,https://www.mouser.com/ProductDetail/TDK/CGA2B2X7R1C224K050B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,TDK,,,
"C703, C704, C705, C706",4,0u1,C_0402_1005Metric,,04023D104JAT2A,,smt,Unpolarized capacitor,https://www.mouser.com/ProductDetail/KYOCERA-AVX/04023D104JA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,KYOCERA AVX,,,
C806,1,470p,C_0402_1005Metric,,GCM1555C2A471JE02D,,smt,Unpolarized capacitor,https://www.mouser.com/ProductDetail/Murata-Electronics/GCM1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,Murata Electronics,,,
C812,1,1n,C_0402_1005Metric,,04025C102KAZ2A,,smt,Unpolarized capacitor,https://www.mouser.com/ProductDetail/KYOCERA-AVX/04025C102KA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,KYOCERA AVX ,,,
D201,1,ESDA7P60-1U1M,ESDA7P60-1U1M,,ESDA7P60-1U1M,,smt,"STMicroelectronics ESDA7P60-1U1M Uni-Directional TVS Diode, 700W peak, 2-Pin QFN1610",https://www.mouser.co.uk/ProductDetail/STMicroelectronics/ES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,STMicroelectronics,511-ESDA7P60-1U1M,https://www.mouser.co.uk/ProductDetail/STMicroelectronics/ES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,
D202,1,BAT30KFILM,BAT30KFILM,,BAT30KFILM,,smt,"STMicroelectronics BAT30KFILM, SMT Schottky Diode, 30V 300mA, 2-Pin SOD-523",https://www.mouser.co.uk/ProductDetail/STMicroelectronics/BA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,STMicroelectronics,511-BAT30KFILM,https://www.mouser.co.uk/ProductDetail/STMicroelectronics/BA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,0.7
"D301, D302",2,LED,LED_0402_1005Metric,,150040RS73240 ,,smt,Light emitting diode,https://www.mouser.com/ProductDetail/Wurth-Elektronik/150040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,Wurth Elektronik,,,
"D401, D402",2,ESDALC6V1-1M2,ESDALC6V11M2,,ESDALC6V1-1M2,,smt,ESD Suppressors / TVS Diodes Low cap TRANSIL,https://www.mouser.co.uk/ProductDetail/STMicroelectronics/ES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,STMicroelectronics,511-ESDALC6V1-1M2,https://www.mouser.co.uk/ProductDetail/STMicroelectronics/ES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,
"D403, D404, D405, D406, D408",5,"PESD3V3L1BA,115",PESD3V3L1BA_115-SOD-323-2,,"PESD3V3L1BA,115",,smt,PESD3V3L1BA - Low capacitance bidirectional ESD protection diode in SOD323,https://www.mouser.co.uk/ProductDetail/Nexperia/PESD3V3L1BA1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,Nexperia,771-PESD3V3L1BA-T/R,https://www.mouser.co.uk/ProductDetail/Nexperia/PESD3V3L1BA1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,1.1
D407,1,LED_RAGB,LED_Kingbright_APFA3010_3x1.5mm_Horizontal,,APFA3010LSEEZGKQBKC,,smt,"RGB LED, red/anode/green/blue",https://www.mouser.com/ProductDetail/Kingbright/APFA3010LSEE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,Kingbright,,,
"FB401, FB801",2,FerriteBead,L_0603_1608Metric,,BBGK00160808601Y00,,smt,Ferrite bead,https://www.mouser.com/ProductDetail/Pulse-Electronics/BBGK0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,Pulse Electronics,,,
FB402,1,FerriteBead,L_0603_1608Metric,,FBMJ1608HM180NTR,,smt,Ferrite bead,https://www.mouser.com/ProductDetail/TAIYO-YUDEN/FBMJ1608HM1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,Taiyo Yuden,,,
"FB701, FB702",2,FerriteBead,BLM15HD182SN1D,,BLM15HD182SN1D,,smt,Ferrite bead,https://www.mouser.com/ProductDetail/Murata-Electronics/BLM1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,Murata Electronics,,,
J201,1,USB_C_Receptacle_USB2.0_16P,USB_C_Receptacle_GCT_USB4105-xx-A_16P_TopMnt_Horizontal,,USB4105-GF-A ,,smt,USB 2.0-only 16P Type-C Receptacle connector,https://www.mouser.com/ProductDetail/GCT/USB4105-GF-A?qs=KUo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,GCT,,,
"J202, J601, J602, J603, J604, J605, J606",7,Screw_Terminal_01x02,"TerminalBlock_Phoenix_MKDS-1,5-2-5.08_1x02_P5.08mm_Horizontal",,1548128,,tht,"Generic screw terminal, single row, 01x02, script generated (kicad-library-utils/schlib/autogen/connector/)",https://www.mouser.com/ProductDetail/Phoenix-Contact/1548128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,Phoenix Contact,,,
"J401, J502",2,Conn_02x05_Counter_Clockwise,62701021621,,62701021621,,tht,"Generic connector, double row, 02x05, odd/even pin numbering scheme (row 1 odd numbers, row 2 even numbers), script generated (kicad-library-utils/schlib/autogen/connector/)",https://www.mouser.com/ProductDetail/Wurth-Elektronik/627010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,Wurth Elektronik,,,
J501,1,CLP-110-02-G-D,CLP-110-02-XXX-D,,CLP-110-02-G-D,,smt,"20 Position Connector Header, Center Strip Contacts Surface Mount",https://www.mouser.com/ProductDetail/Samtec/CLP-110-02-G-D?q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,SAMTEC,200-CLP11002GD,https://www.mouser.co.uk/ProductDetail/Samtec/CLP-110-02-G-D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,
J503,1,Conn_02x08_Counter_Clockwise,PinHeader_2x10_P2.54mm_Vertical,,M20-9720546,,tht,"Generic connector, double row, 02x10, odd/even pin numbering scheme (row 1 odd numbers, row 2 even numbers), script generated (kicad-library-utils/schlib/autogen/connector/)",https://www.mouser.com/ProductDetail/Harwin/M20-9720546?qs=v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,Harwin,,,
J701,1,Screw_Terminal_01x03,"TerminalBlock_Phoenix_MKDS-1,5-3-5.08_1x03_P5.08mm_Horizontal",,1548129,,tht,"Generic screw terminal, single row, 01x03, script generated (kicad-library-utils/schlib/autogen/connector/)",https://www.mouser.com/ProductDetail/Phoenix-Contact/1548129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,Phoenix Contact,,,
J702,1,DM3AT-SF-PEJM5_40_,DM3ATSFPEJM540,,DM3AT-SF-PEJM5(40),,smt,Memory Card Connectors MICRO SD CD CONN STD SMT PUSHPUSH,https://www.mouser.co.uk/ProductDetail/Hirose-Connector/DM3A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,Hirose,798-DM3AT-SF-PEJM540,https://www.mouser.co.uk/ProductDetail/Hirose-Connector/DM3A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,1.83
J801,1,SI-60062-F,Connector-SI60062F,,SI-60062-F,,tht,"Bel-Stewart Female RJ45 Modular Jack, STP, Straight, Through Hole Mount, MagJack",https://www.mouser.com/ProductDetail/Bel-Magnetic-Solutions/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,BelFuse,530-SI-60062-F,,13.84
"L301, L302, L401",3,2u2,L_0603_1608Metric,,MCHK1608T2R2MKN,,smt,Inductor,https://www.mouser.com/ProductDetail/TAIYO-YUDEN/MCHK1608T2R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,TAIYO YUDEN,,,
"L303, L304",2,10u,L_0805_2012Metric,,LQM21FN100M80L,,smt,Inductor,https://www.mouser.com/ProductDetail/Murata-Electronics/LQM2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,Murata Electronics,,,
Q201,1,STL6N3LLH6,STL6N3LLH6,,STL6N3LLH6,,smt,"STMicroelectronics STL6N3LLH6 N-channel MOSFET Transistor, 6 A, 30 V, 6-Pin PowerFLAT",https://www.mouser.co.uk/ProductDetail/STMicroelectronics/ST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,STMicroelectronics,511-STL6N3LLH6,https://www.mouser.co.uk/ProductDetail/STMicroelectronics/ST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,
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
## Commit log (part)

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2026-01-24 basic config - testing board
2026-01-25 configured LED, ADS, ETH - very basic for now
2026-01-27 simple EIP works
2026-01-30 update EIP config
2026-02-01 SDMMC1 on only CM4
2026-02-01 fatfs shared device config - not working
2026-02-04 FatFs working for shared interface
    Clock speed is limited to 20MHz, cant increase for now
2026-02-04 RTOS + eMMC(20MHz) + ETH working
2026-02-06 testing BLE
2026-02-09 ble and eMMC works
2026-03-07 Added RTOS
2026-03-08 Update to FreeRTOS CMSIS v1.0 and UDP is very good
2026-03-23 feature - adding daq, statemachine, and ipc
    Not tested yet
2026-03-24 simple tcp works standalone
2026-03-28 tcp netconn with reconnect
2026-03-30 removed netconn and used raw tcp- works perfect
    1. Auto reconnect
    2. Reconnect after link is down
    This is a good state. So don't use netconn, as due to some reason netconn cannot do auto reconnect on connection loss - IT HANGS!!!
2026-03-30 minor update to ioc
    Fixed default task size to 128
2026-03-30 reduced mem_size for lwip
2026-04-02 minor adjustments and buffer reductions
2026-04-02 changed the RAM and added RAM_D2_ETH
2026-04-02 fixed by increasing FreeRTOS size
2026-04-02 added first heartbeat response
2026-04-03 minor update
2026-04-03 emmc lib being added
2026-04-03 emmc with file counter - appears to be working
    No files in the eMMC memory yet
2026-04-03 configwrite added - appears working
2026-04-03 count and write config works.
2026-04-03 write and read working to eMMC, increase tx to 1024
2026-04-04 added file read and transfer over TCP
2026-04-04 streaming process being tested - randomly
2026-04-05 cm4 can open and mount emmc
2026-04-05 with working readthrough
2026-04-06 following an openamp route - Start
2026-04-06 fixing to get before openAMP executing
2026-04-06 about to re-enable openAMP
2026-04-06 openamp basic implementation
2026-04-10 WIP - Not complete openAMP
    Now planning to minimize the CM4 openAMP operation
2026-04-10 Simple OpenAMP is working
2026-04-10 minor updates - trying to troubleshoot emmc
2026-04-11 added gitignore
2026-04-11 removed the Debug tracking, same for release
2026-04-11 update gitignore
2026-04-11 brought OpenAMP back alive
    Stuck in a problem?
    1. Remove OpenAMP using .ioc file and build
    2. Add OpenAMP using the .ioc file and build
    3. It should bring back the shortcuts and linked file
2026-04-11 Fixed the sdmmc not being included for now
    Just remove and re add the SDMMC1 stuff
2026-04-11 made emmc work by reducing clock rate
2026-04-11 implement file count readers
    1. Can count the .dat file
    2. Can count all files in there
2026-04-11 added getting file size OpenAMP OP
2026-04-12 reading first chunk works
2026-04-12 file offset read implemented and tested
2026-04-12 repeated chunk read
2026-04-12 stream implemented.
2026-04-12 throughput display update for test script
2026-04-12 file streaming without repeated opening - Done
2026-04-12 Increase the buffer size for OpenAMP, TCP chunk
2026-04-12 removed delay from file streaming
2026-04-13 shared memory transfer with increased througput - works
2026-04-13 pointer based TCPStream instead of copy
2026-04-13 start of documentation
2026-04-14 moved files around
2026-04-15 working toward making ADC work - start
    Start of the interface with the ADC
2026-04-15 The ADC is behaving as expected.
2026-04-15 streaming process being tested.
2026-04-15 increasing block size to reduce streaming drops
2026-04-15 restarting stream is fixed
2026-04-16 adc bug on status read fixed
2026-04-17 be able to select sampling rate
2026-04-17 writing to eMMC works for now - still needs some finetuning
2026-04-18 minor update on values output
2026-04-18 DMA enabled with noemmc, no loss
2026-04-18 working to write to emmc
    Not checked if the data written is valid yet
    1. SPI is DMA now
    2. eMMC write works, but interrupts are blocked during write
    2. eMMC sampling rate is not high enough
2026-04-18 working emmc and stream
    Data validity needs to be checked
    1. Sampling rate for eMMC is 1742.7 and stream is 1782 for a required 2000Hz which is OSR 2048.For OSR 2048, we need the sampling rate to be 1953.125
2026-04-18 Increased the block size
2026-04-18 reduced the amount of data written to eMMC
    Only 6 channels for now
2026-04-21 start of interface code
2026-04-21 minor command update
2026-04-21 removed unnecessary commands
2026-04-21 Improving file-ops
2026-04-21 update to make 4 return bytes as well
2026-04-22 library being updated - working stream
2026-04-22 updated some ack parsing
2026-04-22 design improvements
2026-04-22 added conversion to physical values
    Yet to check if they are correct
2026-04-22 removed unwanted commands
2026-04-22 fixed the file streaming and normal streaming
2026-04-22 added more docs on firmware itself
2026-04-22 commanded stream example added
2026-04-23 ability to calibrate pipedin
2026-04-23 offset calibration appears to be working well
2026-04-23 removed tracking of __pycache__
2026-04-24 added new example and readme update
2026-05-03 bug fixed - making filesystem error at higher clk
    1. Make filesystem at lower clock and then increase clock
    2. Updated docs
    3. Added more diagnostics to command 99 and added Python parsing
2026-05-03 fixed multi-board connect issue
    Sometimes the board connects and sometimes it doesn't added reset to the LAN8742 when not connected
2026-05-03 protection CubeMx deletion
2026-05-03 make led useful
2026-05-03 multi board stream tested
    1. csv and bin works
    2. Duration can be set
2026-05-04 added raspberry Pi daemon, cli -- working
2026-05-04 automation friendly and AWS integration
2026-05-04 improved TCP also made easier to update IP
    IP address can be update using the file aems_network_config.h under Core/Inc
    TCP waits for reconnection and sends heartbeat every 10s when not streaming
2026-05-04 readme update
